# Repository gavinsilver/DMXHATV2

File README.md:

# DMXHATV2

DMX Interface to NeoPixel Strip

This is the first Alpha version of the board and software

Alpha Version of the board can be found at https://oshpark.com/shared_projects/N2rTY4Yk 

## DMX Interface to NeoPixel Strip

DMX to Neopixel board. Voltage Isolated DMX interface with separate Arduino Nano CPU’s for DMX and Neopixel driver

If you have tried driving NeoPixel strips from an Arduino and then tried to mix this with DMX then you 
may have hit the problem that the NeoPixel strip requires interrupts to be turned off when it is updated
and when this happens the DMX interface stops receiving data.  Even with small strips you may need to 
wait 50ms before the DMX data recovers.

This project is an attempt to get around this by have two Arduino Nano boards one dedicated to DMX
and the other to controlling the LED strip.  These subsystems communicate over an SPI interface.  The
DMX interface is also fully isolated which most of the cheaper DMX interfaces are not.

The PCB has been produced using KiCAD

The Arduino Code is written in the Arduino IDE

Gavin Silver - 8th June 2018

Copyright (c) Gavin Silver 2018, all rights reserved

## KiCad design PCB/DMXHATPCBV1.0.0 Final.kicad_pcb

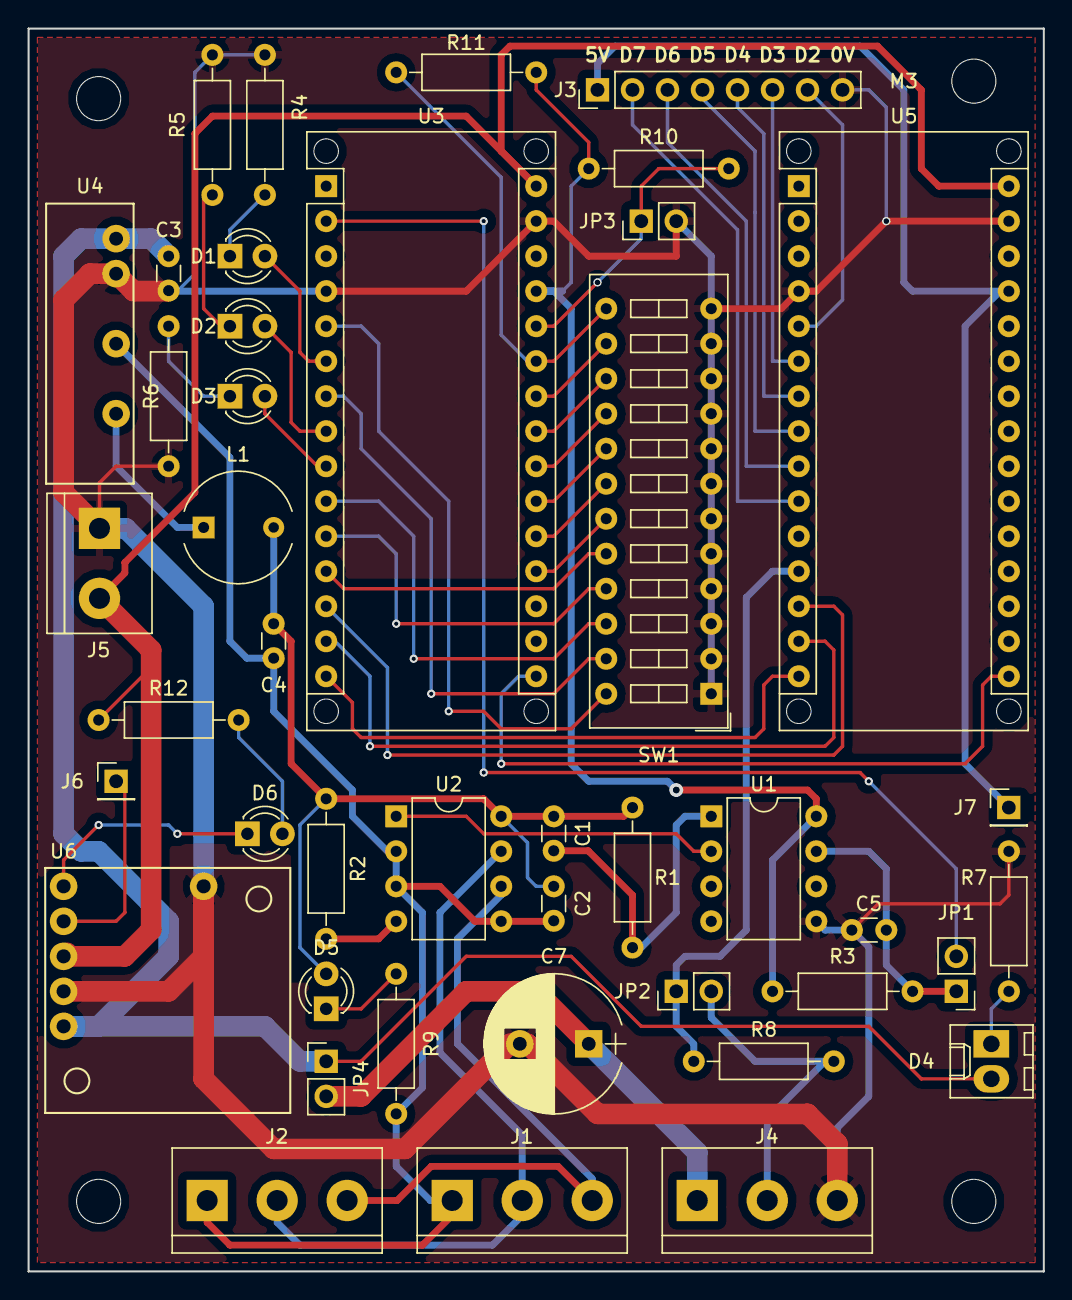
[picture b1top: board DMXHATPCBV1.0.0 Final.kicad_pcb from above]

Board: 2 copper layers, 73.7 x 90.2 mm, 47 parts (0 on the bottom side), 52 nets.

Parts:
C1: 10pF; C_Disc_D3.0mm_W1.6mm_P2.50mm
C2: 10nF; C_Disc_D3.0mm_W1.6mm_P2.50mm
C3, C4: 4.7uF; C_Disc_D3.0mm_W1.6mm_P2.50mm
C5: 22pF; C_Disc_D3.0mm_W1.6mm_P2.50mm
C7: 1000uF; CP_Radial_D10.0mm_P5.00mm
D1, D2, D3, D5, D6: LED; LED_D3.0mm
D4: LED; Molex_KK-6410-02_02x2.54mm_Straight
J1: DMX In; TerminalBlock_bornier-3_P5.08mm
J2: DMX Out; TerminalBlock_bornier-3_P5.08mm
J3: D Outs; Pin_Header_Straight_1x08_Pitch2.54mm
J4: LED Strip; TerminalBlock_bornier-3_P5.08mm
J5: 9V Input; TerminalBlock_bornier-2_P5.08mm
J6: Power EN; Pin_Header_Straight_1x01_Pitch2.54mm
J7: 5V_U5; Pin_Header_Straight_1x01_Pitch2.54mm
JP1: Prog U3 NC; Pin_Header_Straight_1x02_Pitch2.54mm
JP2: R Bypass NO; Pin_Header_Straight_1x02_Pitch2.54mm
JP3: N/A NC; Pin_Header_Straight_1x02_Pitch2.54mm
JP4: Ext Power NC; Pin_Header_Straight_1x02_Pitch2.54mm
L1: 10uH; L1_Radial_D9.0mm
M3, M3#2, M3#3, M3#4: M3; MountingHole_3.2mm_M3
R1: 1.5K; R_Axial_DIN0207_L6.3mm_D2.5mm_P10.16mm_Horizontal
R2: 3.3K; R_Axial_DIN0207_L6.3mm_D2.5mm_P10.16mm_Horizontal
R3: 499; R_Axial_DIN0207_L6.3mm_D2.5mm_P10.16mm_Horizontal
R4, R5, R6, R7, R9: 330; R_Axial_DIN0207_L6.3mm_D2.5mm_P10.16mm_Horizontal
R8, R12: 470; R_Axial_DIN0207_L6.3mm_D2.5mm_P10.16mm_Horizontal
R10, R11: 10K; R_Axial_DIN0207_L6.3mm_D2.5mm_P10.16mm_Horizontal
SW1: SW_DIP_x12; SW_DIP_x12_W7.62mm_Slide
U1: CPC5002; DIP-8_W7.62mm
U2: MAX485; DIP-8_W7.62mm
U3, U5: Nano; Arduino_Nano_WithMountingHoles
U4: REE-0505S
U6: Pololu_D24V22Fx

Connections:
5V_2.5A: C3.1, D4.2, JP4.1, U4.1, U6.5
5V_U5: J3.1, J7.1, U5.27
5v: R3.1, R10.1, R11.1, U1.8, U3.27
9V: J5.2, R12.1, U3.30, U5.30, U6.3
+5V_ISO: C1.1, C2.1, C4.1, D5.2, L1.2, R1.1, R2.1, U2.8
GND: C3.2, C5.2, C7.2, J3.8, J4.3, J5.1, JP3.2, R4.2, R5.2, R6.2, R7.2, SW1.1, SW1.2, SW1.3, SW1.4, SW1.5, SW1.6, SW1.7, SW1.8, SW1.9, SW1.10, SW1.11, SW1.12, U1.5, U3.4, U3.29, U4.2, U5.4, U5.29, U6.4, U6.6
GND_ISO: C2.2, C4.2, J1.1, J2.1, R9.2, U2.2, U2.3, U2.5, U4.4
MISO: U3.15, U5.15
MOSI: U3.14, U5.14
unnamed: C1.2, R1.2, U1.1
unnamed: C5.1, JP1.1, R3.2, U1.7
unnamed: C7.1, J4.1, JP4.2
unnamed: D1.1, R4.1
unnamed: D1.2, U3.6
unnamed: D2.1, R5.1
unnamed: D2.2, U3.8
unnamed: D3.1, R6.1
unnamed: D3.2, U3.9
unnamed: D4.1, R7.1
unnamed: D5.1, R9.1
unnamed: D6.1, U6.1
unnamed: D6.2, R12.2
unnamed: J1.2, J2.2, U2.7
unnamed: J1.3, J2.3, U2.6
unnamed: J3.2, U5.10
unnamed: J3.3, U5.9
unnamed: J3.4, U5.8
unnamed: J3.5, U5.7
unnamed: J3.6, U5.6
unnamed: J3.7, U5.5
unnamed: J4.2, JP2.2, R8.2
unnamed: J6.1, U6.2
unnamed: JP1.2, U3.2
unnamed: JP2.1, R8.1, U5.12
unnamed: JP3.1, R10.2, U3.26
unnamed: L1.1, U4.6
unnamed: R2.2, U2.4
unnamed: R11.2, SW1.13, U3.25
unnamed: SW1.14, U3.24
unnamed: SW1.15, U3.23
unnamed: SW1.16, U3.22
unnamed: SW1.17, U3.21
unnamed: SW1.18, U3.20
unnamed: SW1.19, U3.19
unnamed: SW1.20, U3.12
unnamed: SW1.21, U3.11
unnamed: SW1.22, U3.10
unnamed: SW1.23, U3.7
unnamed: SW1.24, U3.5
unnamed: U1.2, U2.1
SCK: U3.16, U5.16
SS: U3.13, U5.13

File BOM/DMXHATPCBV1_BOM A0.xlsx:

| Hat Project BOM
 | 3 | Boards Required |  |  |  |  |  | xx | = we have enough
Id | Designator | Package | Designation | Required per Board | Unit Cost | Cost Per Board | Order Units | Qty in Stock | On order | Required | Order | Supplier and ref
1 | U5,U3 | Arduino_Nano_WithMountingHoles | Nano | 2 | 2.9966666666666666 | 5.9933333333333332 | 3 | 7 |  | 6 |  | https://www.amazon.co.uk/gp/product/B072BMYZ18
2 | U1 | DIP-8_W7.62mm | CPC5002 | 1 | 2.0489999999999999 | 2.0489999999999999 |  | 16 |  | 3
3 | M3,M3,M3,M3 | MountingHole_3.2mm_M3 | M3 |  |  |  |  |  |  | 0 |  | no part required
4 | D1,D2,D3,D5 | LED_D3.0mm | LED | 4 |  | 0 |  | 12 |  | 12
5 | R8 | R_Axial_DIN0207_L6.3mm_D2.5mm_P10.16mm_Horizontal | 470 | 1 |  | 4.1799999999999997E-2 |  | 49 |  | 3
6 | C1 | C_Disc_D3.0mm_W1.6mm_P2.50mm | 10pF | 1 |  | 0 |  | 9 |  | 3
7 | C3,C4 | C_Disc_D3.0mm_W1.6mm_P2.50mm | 4.7uF | 2 |  | 0.19900000000000001 |  | 8 |  | 6
8 | C5 | C_Disc_D3.0mm_W1.6mm_P2.50mm | 22pF | 1 |  | 0 |  | 9 |  | 3
9 | R1 | R_Axial_DIN0207_L6.3mm_D2.5mm_P10.16mm_Horizontal | 1.5K | 1 |  | 4.1799999999999997E-2 |  | 49 |  | 3
10 | R2 | R_Axial_DIN0207_L6.3mm_D2.5mm_P10.16mm_Horizontal | 3.3K | 1 |  | 0 |  | 48 |  | 3
11 | R3 | R_Axial_DIN0207_L6.3mm_D2.5mm_P10.16mm_Horizontal | 499 | 1 |  | 0.13400000000000001 |  | 20 |  | 3
12 | R4,R5,R6,R9,R7 | R_Axial_DIN0207_L6.3mm_D2.5mm_P10.16mm_Horizontal | 330 | 5 |  | 0 |  | 40 |  | 15
13 | C2 | C_Disc_D3.0mm_W1.6mm_P2.50mm | 10nF | 1 |  | 0 |  | 9 |  | 3
14 | JP2,JP3,JP4 | Pin_Header_Straight_1x02_Pitch2.54mm | Jumper_NO | 3 |  | 0 |  | 9 |  | 9
15 | U2 | DIP-8_W7.62mm | MAX485 | 1 |  | 0.44 |  | 9 |  | 3
16 | D4 | Molex_KK-6410-02_02x2.54mm_Straight | LED | 1 |  | 0 |  | 3 |  | 3
17 | C7 | CP_Radial_D10.0mm_P5.00mm | 1000uF | 1 |  | 0 |  | 4 |  | 3
18 | SW1 | SW_DIP_x12_W7.62mm_Slide | SW_DIP_x12 | 1 |  | 0.41599999999999998 |  | 4 |  | 3
19 | R10,R11 | R_Axial_DIN0207_L6.3mm_D2.5mm_P10.16mm_Horizontal | 10K | 2 |  | 4.1799999999999997E-2 |  | 48 |  | 6
20 | J5 | TerminalBlock_bornier-2_P5.08mm | 9V Input | 1 |  | 0 |  | 4 |  | 3
21 | J1,J2 | TerminalBlock_bornier-3_P5.08mm | DIN-3 & LED_Strip | 3 |  | 9.5000000000000001E-2 |  | 20 |  | 9
22 | J4 | TerminalBlock_bornier-3_P5.08mm | as above
23 | U4 | REE-0505S | REE-0505S | 1 |  | 3.08 |  | 0 | 3 | 3
24 | U6 | Pololu_D24V22Fx | Pololu_D24V22Fx | 1 | 6.72 | 6.72 |  | 1 | 2 | 3 |  | http://www.hobbytronics.co.uk/d24v22f5-5v-step-down-regulato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
25 | L1 | L1_Radial_D9.0mm | 10uH | 1 | 0.28799999999999998 | 0.28799999999999998 |  | 9 |  | 3
26 | J3 | Pin_Header_Straight_1x08_Pitch2.54mm | Conn_01x08 | 1 |  | 0 |  | 3 |  | 3
 |  | Other Components
 |  | PCB |  | 1 | 18.38 | 18.38 |  |  | 3 | 3
 |  | Cable Glands |  | 2 | 0.91700000000000004 |  |  | 11 |  | 6
 |  | 3 Way DMX DIN Lead |  | 1 | 3.95 |  |  | 0 | 3 | 3 |  | Kenable?
 |  | 3 Way Aviation DIN Connector |  | 1 | 0.51900000000000002 |  |  | 9 |  | 3
 |  | Hammond Box |  | 1 |  |  |  | 1 |  | 3 | 2 | RS ?
 |  | M3 Nylon Mounting Post |  | 4 |  |  |  | 30 |  | 12
 |  | M3 Screw |  | 4 |  |  |  | 30 |  | 12
 |  | M3 Nylon Nut |  | 4 |  |  |  | 30 |  | 12
 |  | Power LED gland |  | 1 |  |  |  | 3 |  | 3
 |  | Power LED 5mm RED |  | 1 |  |  |  | 3 |  | 3
 |  | Rubber Feet |  | 4 |  |  |  | 12 |  | 12
 |  | 2 Pin Header |  | 3 |  |  |  | 9 |  | 9
 |  | 2 Pin Jumper with grip |  | 3 |  |  |  | 0 | 10 | 9 |  | RS ?
 |  | 8 Pin Header |  | 1 |  |  |  | 3 |  | 3
 |  | DC Power Connector |  | 1 | 0.59799999999999998 |  |  | 3 |  | 3
 |  | 3 PIN GX20 Aviation Plug |  |  | 5.7 |  |  | 2 |  | 0
 |  | 2 PIN GX20 Aviation Plug |  |  | 5.6 |  |  |  | 2 | 0
 |  | 8A PSU |  |  |  |  |  |  | 1 | 0
 |  |  |  |  | Total | 37.919733333333333
 | RS Order
 | Qty | Description | Part Number
 | 2 | Hammond Box
 | Keanbale Order
 | Qty | Description | Part Number
 | Ebay Order
 | Qty | Description | Part Number
 | Amazon Order
 | Qty | Description | Part Number
 | 2 | 8A 5V PSU

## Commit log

2018-06-08 PCB Added
    This is the final version of the Alpha1 PCB sent to OSH Park for fabrication
2018-06-08 add (C) details
    Add (C) Details
2018-09-10 1st Board Test Version
    Changed LED's to 50
    Removed some debug code
    Change SPI Delay to 40 Micrososconds to stop occasional SPI data read corruptions
2018-09-10 1st Board Test Version
    Added function to Fake DMX data using pin 12 Colour cycles RGBW ever 25 cycles through Void Loop ()
    Fixed issue with pins A6 & A7 not working with digital reads
2018-09-10 Bill of Materials Added
    Bill of Materials in Excel format required to build board
2018-09-10 Board in Case
    Pcture of the board assemebeled in the case
